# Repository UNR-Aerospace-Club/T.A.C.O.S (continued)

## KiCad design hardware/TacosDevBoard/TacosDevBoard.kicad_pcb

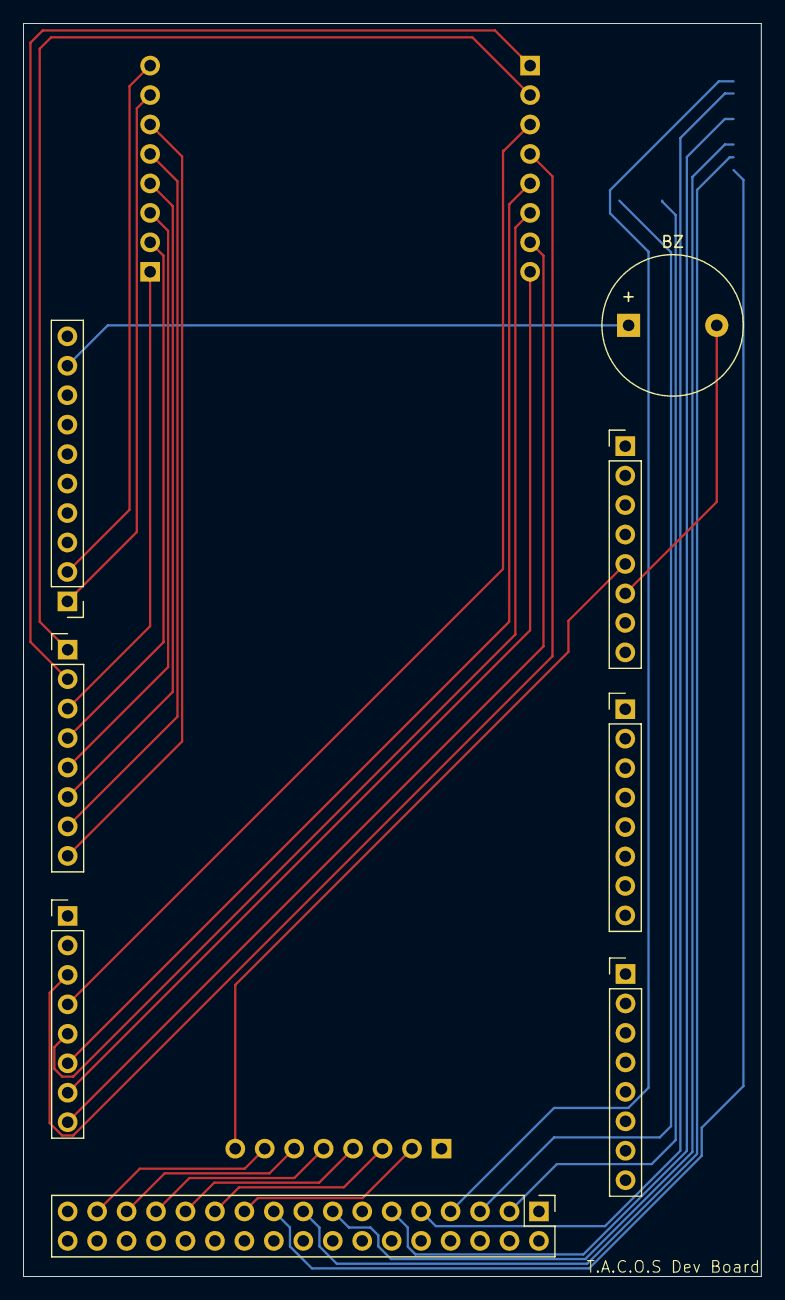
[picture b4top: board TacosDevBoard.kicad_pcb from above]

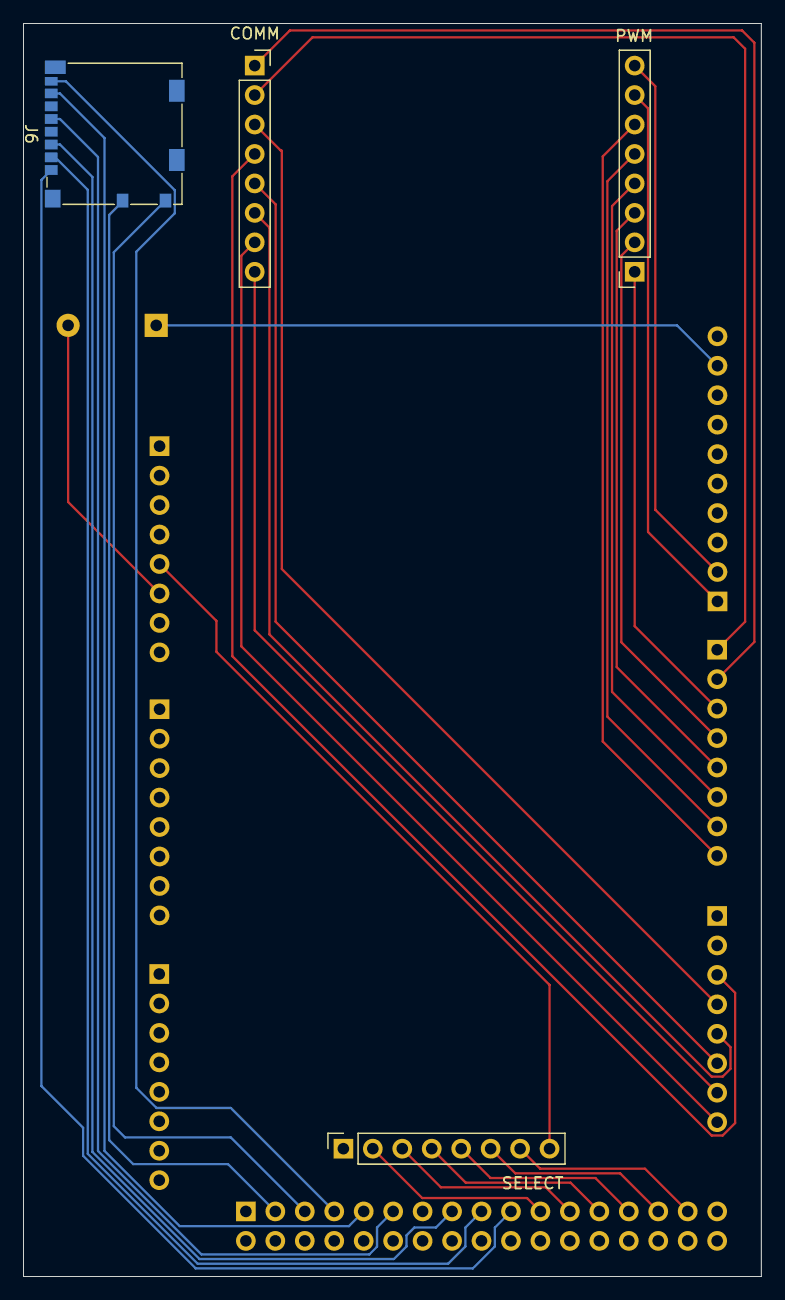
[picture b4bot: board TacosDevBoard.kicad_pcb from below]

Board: 2 copper layers, 63.6 x 108.1 mm, 12 parts (4 on the bottom side), 35 nets.

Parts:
BZ: Buzzer; Buzzer_12x9.5RM7.6
COMM: Conn_01x08_Socket; PinSocket_1x08_P2.54mm_Vertical
J1, J2, J3, J4, J5: Conn_01x08_Socket; PinHeader_1x08_P2.54mm_Vertical
J6: Micro_SD_Card_Det2; microSD_HC_Molex_104031-0811
J8: Conn_02x17_Odd_Even; PinHeader_2x17_P2.54mm_Vertical
J9: Conn_01x10_Pin; PinHeader_1x10_P2.54mm_Vertical
PWM: Conn_01x08_Socket; PinSocket_1x08_P2.54mm_Vertical
SELECT: Conn_01x08_Socket; PinSocket_1x08_P2.54mm_Vertical

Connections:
+5V: J3.5, J8.1, J8.2, SELECT.8
D22: J8.31, SELECT.7
D24: J8.29, SELECT.6
D26: J8.27, SELECT.5
D28: J8.25, SELECT.4
D30: J8.23, SELECT.3
D32: J8.21, SELECT.2
D52: BZ.1 (+), J9.9
GND: BZ.2 (-), J3.6, J6.11 (SHIELD), J8.33, J8.34, SELECT.1
RX0: COMM.2, J5.1
RX1: COMM.4, J4.3
RX2: COMM.6, J4.5
RX3: COMM.8, J4.7
SD_CLK: J6.5 (CLK), J8.11
SD_CMD: J6.3 (CMD), J8.15
SD_DAT0: J6.7 (DAT0), J8.9
SD_DAT1: J6.8 (DAT1), J8.7
SD_DAT2: J6.1 (DAT2), J8.19
SD_DAT3/CD: J6.2 (DAT3/CD), J8.17
SD_DET_A: J6.10 (DET_A), J8.5
SD_DET_B: J6.9 (DET_B), J8.3
TX0: COMM.1, J5.2
TX1: COMM.3, J4.4
TX2: COMM.5, J4.6
TX3: COMM.7, J4.8
VDD: J3.4, J6.4 (VDD)
VSS: J3.7, J6.6 (VSS)
~D2: J5.3, PWM.1
~D3: J5.4, PWM.2
~D4: J5.5, PWM.3
~D5: J5.6, PWM.4
~D6: J5.7, PWM.5
~D7: J5.8, PWM.6
~D8: J9.1, PWM.7
~D9: J9.2, PWM.8

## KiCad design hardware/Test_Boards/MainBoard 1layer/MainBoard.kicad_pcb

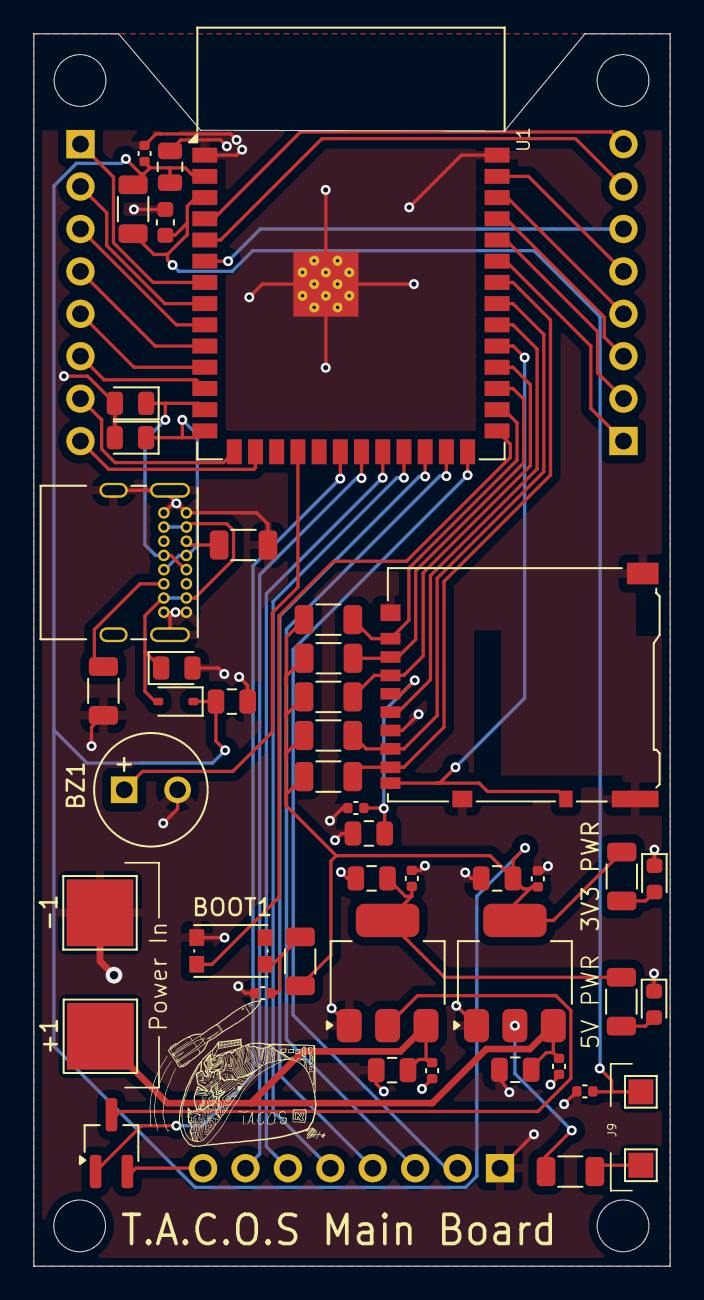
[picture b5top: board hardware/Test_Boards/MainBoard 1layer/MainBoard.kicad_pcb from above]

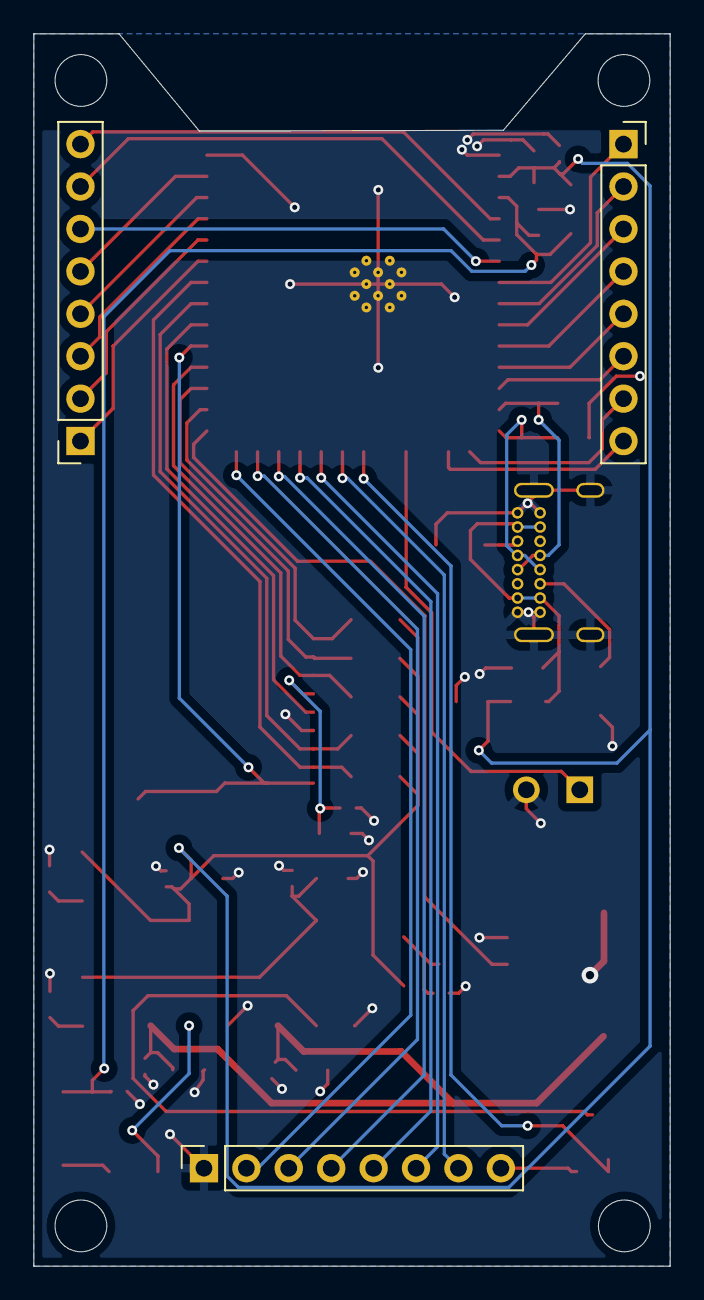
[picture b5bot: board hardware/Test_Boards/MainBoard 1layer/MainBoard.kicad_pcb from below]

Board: 2 copper layers, 38.1 x 73.8 mm, 49 parts (3 on the bottom side), 46 nets.

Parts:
+1: LIPO GND; TestPoint_Pad_4.0x4.0mm
-1: LIPO PWR; TestPoint_Pad_4.0x4.0mm
BOOT1: RESET; SW_Push_1P1T_NO_CK_KMR2
BZ1: Buzzer; MagneticBuzzer_Kingstate_KCG0601
C1, C2, C4, C8, C10, C12, C15: 10uF; C_0805_2012Metric
C3, C5, C6, C7, C9, C11, C16: 0u1F; C_0402_1005Metric
C13: 100nF; C_0402_1005Metric
C14: 1uF; C_0603_1608Metric
D1: 1N5819WS; D_SOD-323
D2, D3, D4: D_TVS_Small_Filled; D_0805_2012Metric
D5, D6: PWRLED; LED_0603_1608Metric
J1, J2, J3: Conn_01x08_Socket; PinSocket_1x08_P2.54mm_Vertical
J4: Micro_SD_Card_Det2; microSD_HC_Hirose_DM3AT-SF-PEJM5
J5: USB_C_Receptacle_USB2.0_16P; USB_C_Receptacle_GCT_USB4085
J8: En_A; TestPoint_Pad_1.5x1.5mm
J9: En_B; TestPoint_Pad_1.5x1.5mm
Q1: MMBT2222A; SOT-23W_Handsoldering
R1, R2: 5k1; R_1206_3216Metric
R3, R6: 75; R_1206_3216Metric
R4, R5, R7, R8, R9, R10, R12, R13: 10k; R_1206_3216Metric
U1: ESP32-S3-WROOM-1
U2: AMS1117-3.3; SOT-223-3_TabPin2
U3: AMS1117-5.0; SOT-223-3_TabPin2

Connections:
BZR: BZ1.1 (+), U1.18 (IO10)
CHIP_PU: C7.1, C14.1, J9.1, R7.2, U1.3 (EN)
DATA0: J3.8, U1.4 (IO4)
DATA1: J3.7, U1.5 (IO5)
DATA2: J3.6, U1.6 (IO6)
DATA3: J3.5, U1.39 (IO1)
DATA4: J3.4, U1.38 (IO2)
DATA5: J3.3, U1.37 (TXD0)
DATA6: J3.2, U1.36 (RXD0)
DATA7: J3.1, U1.35 (IO42)
DATA8: J2.1, U1.7 (IO7)
DATA9: J2.2, U1.8 (IO15)
DATA10: J2.3, U1.9 (IO16)
DATA11: J2.4, U1.10 (IO17)
DATA12: J2.5, U1.11 (IO18)
DATA13: J2.6, U1.12 (IO8)
DATA14: J2.7, U1.15 (IO3)
DATA15: J2.8, U1.16 (IO46)
ESP_3V3: C1.1, C4.1, C5.1, C12.1, C13.1, C15.1, C16.1, D1.1 (K), J4.4 (VDD), R3.1, R4.1, R5.1, R7.1, R8.1, R9.1, R10.1, R12.1, R13.1, U1.2 (3V3), U2.2 (VO)
GPIO0: BOOT1.2, C6.1, R4.2, U1.27 (IO0)
HATS_ENABLE: Q1.1 (B), U1.20 (IO12)
I0: J1.2, U1.26 (IO45)
I1: J1.3, U1.25 (IO48)
I2: J1.4, U1.24 (IO47)
I3: J1.5, U1.23 (IO21)
I4: J1.6, U1.22 (IO14)
LIPO GND: -1.1, BOOT1.1, BZ1.2 (-), C1.2, C2.2, C3.2, C4.2, C5.2, C6.2, C7.2, C8.2, C9.2, C10.2, C11.2, C12.2, C13.2, C14.2, C15.2, C16.2, D2.2 (A2), D3.2 (A2), D4.2 (A2), D5.1 (K), D6.1 (K), J1.1, J4.6 (VSS), J4.11 (SHIELD), J5.A1 (GND), J5.A12 (GND), J5.B1 (GND), J5.B12 (GND), J5.S1 (SHIELD), R1.2, R2.2, U1.1 (GND), U1.40 (GND), U1.41 (GND), U2.1 (GND), U3.1 (GND)
LIPO PWR: +1.1, C2.1, C3.1, C8.1, C9.1, U2.3 (VI), U3.3 (VI)
unnamed: D1.2 (A), D2.1 (A1), J5.A4 (VBUS), J5.A9 (VBUS), J5.B4 (VBUS), J5.B9 (VBUS)
unnamed: D5.2 (A), R3.2
unnamed: D6.2 (A), R6.2
unnamed: J1.8, Q1.2 (E)
unnamed: J5.A5 (CC1), R2.1
unnamed: J5.B5 (CC2), R1.1
unnamed: J8.1, R5.2
SD_CLK: J4.5 (CLK), U1.32 (IO39)
SD_CMD: J4.3 (CMD), R10.2, U1.30 (IO37)
SD_DAT0: J4.7 (DAT0), R12.2, U1.33 (IO40)
SD_DAT1: J4.8 (DAT1), R13.2, U1.34 (IO41)
SD_DAT2: J4.1 (DAT2), R8.2, U1.28 (IO35)
SD_DAT3: J4.2 (DAT3/CD), R9.2, U1.29 (IO36)
SD_DET: J4.9 (DET_B), J4.10 (DET_A), U1.31 (IO38)
SELECT RETURN: J1.7, U1.21 (IO13)
USB+: D4.1 (A1), J5.A6 (D+), J5.B6 (D+), U1.14 (USB_D+)
USB-: D3.1 (A1), J5.A7 (D-), J5.B7 (D-), U1.13 (USB_D-)
VCC_5V: C10.1, C11.1, Q1.3 (C), R6.1, U3.2 (VO)

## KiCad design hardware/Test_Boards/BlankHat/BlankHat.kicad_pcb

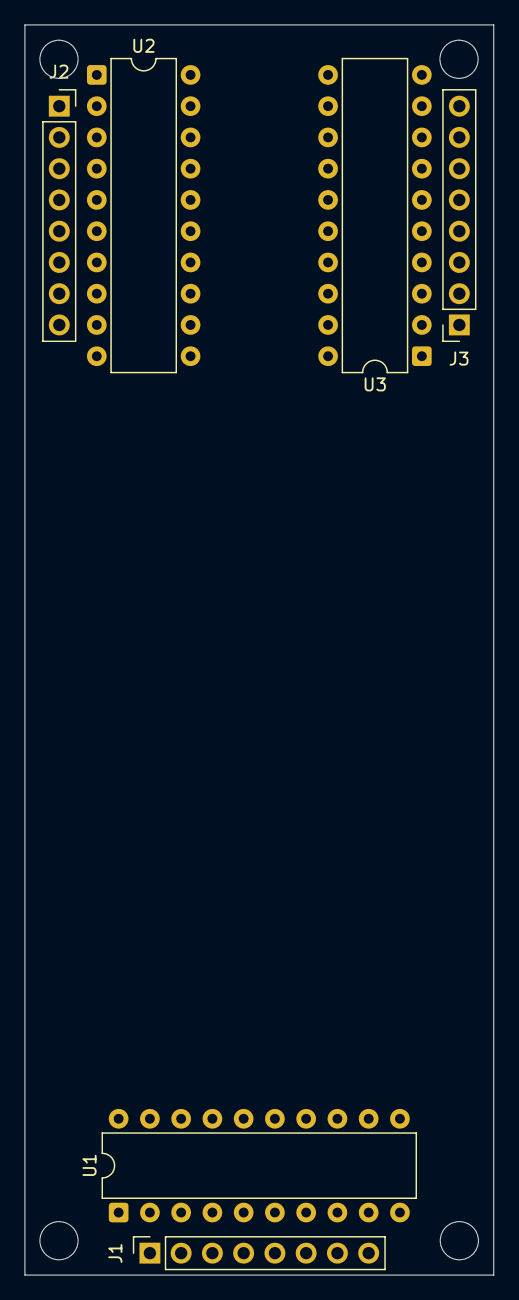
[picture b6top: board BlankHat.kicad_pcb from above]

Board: 2 copper layers, 38.1 x 101.6 mm, 6 parts (0 on the bottom side), 25 nets, no tracks yet.

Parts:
J1, J2, J3: Conn_01x08_Socket; PinSocket_1x08_P2.54mm_Vertical
U1: 74HC688; DIP-20_W7.62mm
U2, U3: 74HC245; DIP-20_W7.62mm

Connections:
+5V: J1.8, U1.3 (R0), U1.20 (VCC), U2.1 (A->B), U2.2 (A0), U2.20 (VCC), U3.1 (A->B), U3.20 (VCC)
GND: J1.1, U1.1 (G), U1.5 (R1), U1.7 (R2), U1.9 (R3), U1.10 (GND), U1.12 (R4), U1.14 (R5), U1.15 (P6), U1.16 (R6), U1.17 (P7), U1.18 (R7), U2.10 (GND), U3.10 (GND)
I0: J1.2, U1.2 (P0)
I1: J1.3, U1.4 (P1)
I2: J1.4, U1.6 (P2)
I3: J1.5, U1.8 (P3)
I4: J1.6, U1.11 (P4)
I5: J1.7, U1.13 (P5)
unnamed: J2.1, U2.18 (B0)
unnamed: J2.2, U2.3 (A1)
unnamed: J2.3, U2.4 (A2)
unnamed: J2.4, U2.5 (A3)
unnamed: J2.5, U2.6 (A4)
unnamed: J2.6, U2.7 (A5)
unnamed: J2.7, U2.8 (A6)
unnamed: J2.8, U2.9 (A7)
unnamed: J3.1, U3.2 (A0)
unnamed: J3.2, U3.3 (A1)
unnamed: J3.3, U3.4 (A2)
unnamed: J3.4, U3.5 (A3)
unnamed: J3.5, U3.6 (A4)
unnamed: J3.6, U3.7 (A5)
unnamed: J3.7, U3.8 (A6)
unnamed: J3.8, U3.9 (A7)
unnamed: U1.19 (P=R), U2.19 (CE), U3.19 (CE)

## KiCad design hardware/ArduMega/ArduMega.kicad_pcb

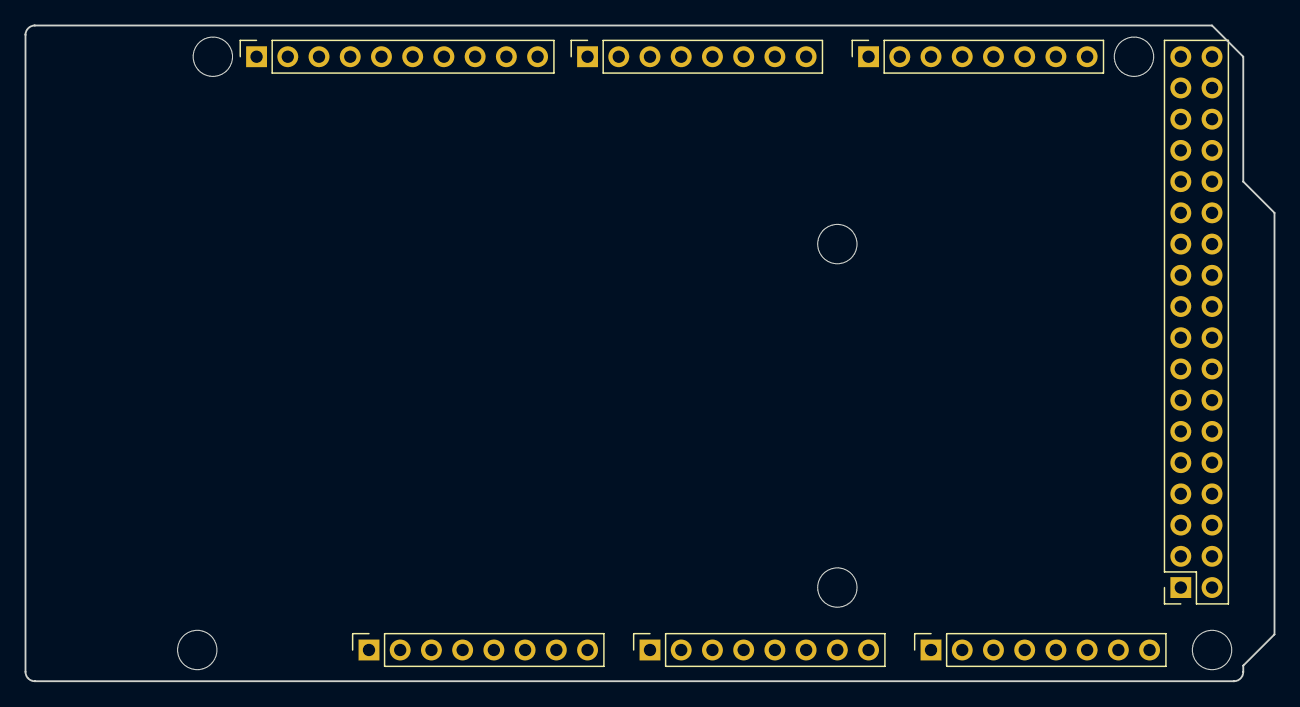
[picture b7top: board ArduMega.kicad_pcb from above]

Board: 2 copper layers, 101.6 x 53.3 mm, 13 parts (0 on the bottom side), 4 nets, no tracks yet.

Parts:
J1: Power; PinSocket_1x08_P2.54mm_Vertical
J2: PWM; PinSocket_1x10_P2.54mm_Vertical
J3, J5: Analog; PinSocket_1x08_P2.54mm_Vertical
J4: PWM; PinSocket_1x08_P2.54mm_Vertical
J6: Communication; PinSocket_1x08_P2.54mm_Vertical
J7: Digital; PinSocket_2x18_P2.54mm_Vertical
MH1, MH2, MH3, MH4, MH5, MH6: MountingHole_3.2mm

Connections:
+5V: J1.5, J7.35, J7.36
/SCL/21: J2.1, J6.8
/SDA/20: J2.2, J6.7
GND: J1.6, J1.7, J2.4, J7.1, J7.2

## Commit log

2025-09-15 Baseline layout for T.A.C.O.S dev board
2025-09-15 added main ino file and software folder
2025-09-15 Add buzzer to Dev Board
2025-09-15 Ignore lock files for kicad
2025-09-16 started working on dummy board - not finished
2025-09-16 Add orthogonal dimensions to dev board
2025-09-16 Finish First Dummy Hat Design
2025-09-17 Update dummy board schematic
    Update dummy board schematic to use octal tranciever chip. Issues. Data pins are now one way and do not support analog.
2025-09-17 Finish dev board. Limitations still apply.
2025-09-17 finished mega pcb
2025-09-18 finished dev board
2025-09-18 added blank hat
2025-09-18 applied noconnects to unused dev board pins
2025-09-18 started adding SD card
2025-09-19 added sd card to dev board
2025-09-19 added power for sd
2025-09-19 started adding data arrays
2025-09-19 add not gate to dummy board for 16 data pins
2025-09-21 finished dev board rewire
2025-09-21 cleaned up silks
2025-09-21 cleaned up silkslides
2025-09-22 started working on hat detection and selection
2025-09-24 finished hat container
2025-09-26 started working on main board
2025-09-26 added more stuff to main board
2025-09-26 finished usb and voltage regulator
2025-09-27 added buttons to main board
2025-09-29 added another voltage regulator
2025-09-29 added lots of things to main board
2025-09-30 more main board stuff
2025-09-30 finished main board
2025-09-30 added power from usb to main board
2025-09-30 added no connects to our two empty pins on the esp32
2025-10-01 started working on blank smd hat:
2025-10-01 tacos logo and font change
2025-10-01 added power flag to ground
2025-10-02 designing new main board
2025-10-02 main boards almost done:
2025-10-03 started wiring main boards
2025-10-03 connector footprints
2025-10-03 fix margin on connector footprint
2025-10-03 wide board lel
2025-10-03 main board stuff
2025-10-04 start arranging componnets for rack layout
2025-10-06 started final traces
2025-10-06 start on rack model
2025-10-06 Revert "merge? i might have messed it up"
    This reverts commit 9783b900dc87fa86d5773213ec3461e06766d3d4, reversing
    changes made to c60a9f34725409086c7bd1e4ee39c0fff9320fd7.
2025-10-06 finished 1x1 main board
2025-10-06 replaced files with backup - were broken
2025-10-06 made boards actually square lmao
2025-10-06 finished main board w/ ground and power planes
2025-10-06 started working on firmware stuff
2025-10-07 remove freecad backups and clean up usb c port
2025-10-07 added emulation board
2025-10-10 added voltage switcher - still needs to be routed
2025-10-12 added USB power switching
2025-10-13 changing stuff to make it pin based, not bool based
2025-10-20 more firmware dev for hat select
2025-10-27 started adding subsystems for the emulation hat
2025-10-29 more emulation hat stuff
2025-11-05 started making dummy snake
2025-11-06 finished snake
2025-11-07 emulation
2025-11-14 correct connector placement
2025-11-14 emulation hat and stuff
2025-11-14 start on rocket hat
2025-11-16 Rocket hat sensor libraries
2025-11-16 Rocket Hat schematic done
2025-11-17 rocket hat footprints done
2025-11-17 rocket hat connector labels
2025-11-17 added power passthrough via data pins WTFFFF
2025-11-17 start routing
2025-11-18 Work more on traces for rocket hat and add dipswitch
2025-11-19 keep routing rocket hat
2025-11-19 rocker hat work
2025-11-19 fixed main hat
2025-11-20 rocket hat finished routing 4 layer
2025-11-20 more main board polish
2025-11-20 rocket hat done
2025-11-20 remove rocket hat c5 silkscreen
2025-11-23 generated assembly files
2025-11-23 sanity checked, ready for production
2025-11-23 made the blank hat with correct footprint
2025-11-24 changed voltage selector to actually work
